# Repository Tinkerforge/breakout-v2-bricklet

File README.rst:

Breakout Bricklet 2.0
=====================

**This Bricklet is currently in development.**

This repository contains the hardware design files.

Repository Content
------------------

hardware/:
 * Contains KiCad project files and additionally schematics as PDF

Hardware
--------

The hardware is designed with the open source EDA Suite KiCad
(http://www.kicad.org). Before you are able to open the files,
you have to install the Tinkerforge kicad-libraries
(https://github.com/Tinkerforge/kicad-libraries). You can either clone
them directly in hardware/ or clone them in a separate folder and
symlink them into hardware/
(ln -s kicad_path/kicad-libraries project_path/hardware). After that you
can open the .pro file in hardware/ with KiCad and from there view and
modify the schematics and the PCB layout.

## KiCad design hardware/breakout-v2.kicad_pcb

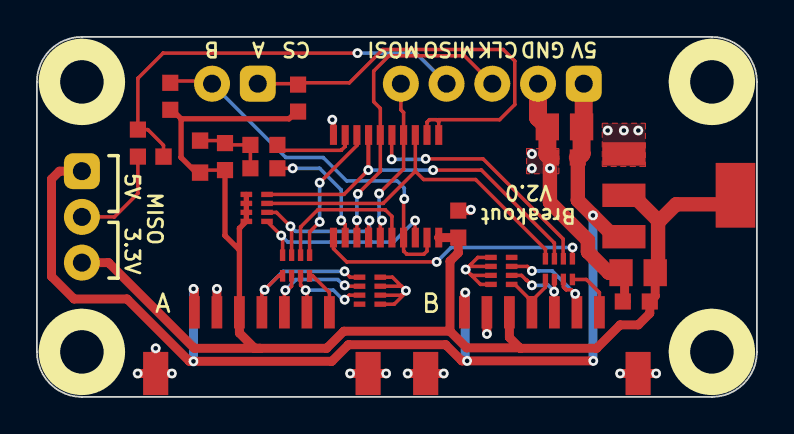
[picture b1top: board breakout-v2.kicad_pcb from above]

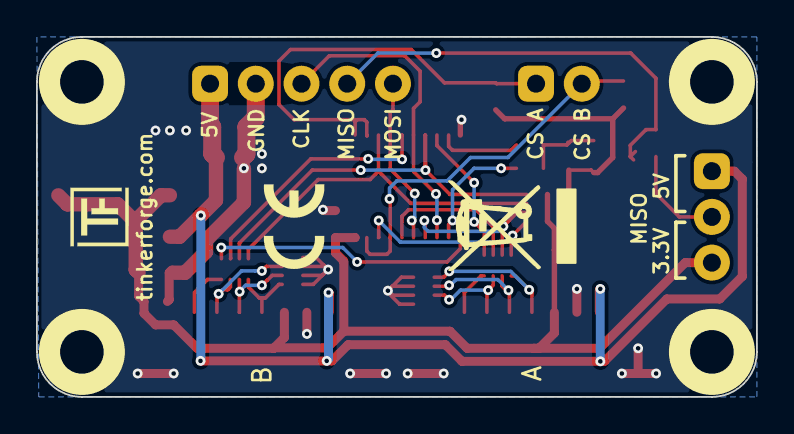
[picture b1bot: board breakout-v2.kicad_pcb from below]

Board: 2 copper layers, 40.0 x 20.0 mm, 30 parts (2 on the bottom side), 28 nets.

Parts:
C1, C3: 10uF; C0805E
C2, C4: 1uF; C0603F
C5: 100nF; C0603F
CP1, CP2: 220pF; 4X0402
P1: Port A; CON-SENSOR2
P2: CONN_01X05; pin_array_1x5-P2mm_D1mm
P3: CONN_01X02; pin_array_1x2-P2mm_D1mm
P4: CONN_01X03; pin_array_1x3-P2mm_D1mm
P5: Port B; CON-SENSOR2
Q1: 2N7002; SOT23GDS
R1, R2, R3, R4: 10k; R0603F
R5, R6: 100; R0603F
RP1, RP2: 82; 4X0402
RP3: 100k; 4X0402
U1: LD1117; SOT-223
U2: 74AHC244; TSSOP20
U3, U4, U5, U6: DRILL; DRILL_NP
VAL: CE_5mm
VAL#2: WEEE_7mm

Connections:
+3.3VP: C3.1, C4.1, C5.1, P1.3, P4.3, P5.3, Q1.G, R2.1, R3.1, R4.1, RP3.1, RP3.2, RP3.3, RP3.4, U1.2, U2.20
+5V: C1.1, C2.1, P1.1, P2.1, P4.1, P5.1, U1.3
CLK: P2.3, U2.6, U2.13
CS_A: P3.1, R4.2, U2.1, U2.2
CS_B: P3.2, R3.2, U2.17, U2.19
GND: C1.2, C2.2, C3.2, C4.2, C5.2, CP1.5, CP1.6, CP1.7, CP1.8, CP2.5, CP2.6, CP2.7, CP2.8, P1.2, P1.EP, P2.2, P5.2, P5.EP, U1.1, U2.10
MISO: P2.4, Q1.D, R1.2
MOSI: P2.5, U2.4, U2.15
unnamed: CP1.1, P1.4, RP1.5
unnamed: CP1.2, P1.5, RP1.6
unnamed: CP1.3, P1.6, RP1.7
unnamed: CP2.1, P5.4, RP2.5
unnamed: CP2.2, P5.5, RP2.6
unnamed: CP2.3, P5.6, RP2.7
unnamed: P1.7, RP1.8
unnamed: P4.2, R1.1
unnamed: P5.7, RP2.8
unnamed: Q1.S, R2.2, R5.2, R6.2
unnamed: R5.1, U2.12
unnamed: R6.1, U2.9
unnamed: RP1.1, U2.8
unnamed: RP1.2, U2.16
unnamed: RP1.3, RP3.6, U2.14
unnamed: RP1.4, RP3.5, U2.18
unnamed: RP2.1, U2.11
unnamed: RP2.2, U2.5
unnamed: RP2.3, RP3.8, U2.7
unnamed: RP2.4, RP3.7, U2.3

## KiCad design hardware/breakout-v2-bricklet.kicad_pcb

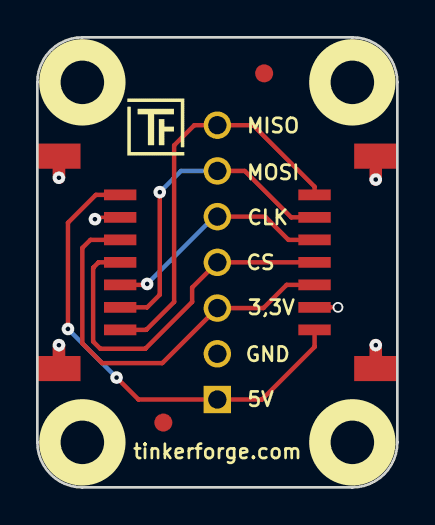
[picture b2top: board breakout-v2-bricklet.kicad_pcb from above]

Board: 2 copper layers, 20.0 x 25.0 mm, 10 parts (1 on the bottom side), 7 nets.

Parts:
Fiducial_Mark: VAL**; Fiducial_Mark
Fiducial_Mark#2: VAL**; Fiducial_Mark
P1, P3: CON-SENSOR2
P2: CONN_01X07; PIN_ARRAY-7X1
U1, U2, U3, U4: DRILL; DRILL_NP
VAL: CE_5mm

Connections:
GND: P1.2, P1.EP, P2.2, P3.2, P3.EP
unnamed: P1.1, P2.1, P3.1
unnamed: P1.3, P2.3, P3.3
unnamed: P1.4, P2.4, P3.4
unnamed: P1.5, P2.5, P3.5
unnamed: P1.6, P2.6, P3.6
unnamed: P1.7, P2.7, P3.7

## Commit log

2017-02-27 Add readme
2017-02-27 Initial check in
2017-02-27 Add schematic
2017-02-27 Add PCB
2017-02-28 Add WEEE, CE and TF logos
2017-02-28 Fix labeling and add fiducial marks
2017-03-01 Fix CE logo
2018-02-20 Add .gitignore
2018-02-20 Cleanup KiCad libraries config
    Ensure LibDir=kicad-libraries and LibName1=tinkerforge.
    Remove special library.
2018-05-14 Add 3d information
2018-05-14 Add 3d model (*.FCStd & *.step)
2019-05-13 fix filenames
2020-06-18 new schematic
2020-06-19 new design
2020-06-22 edited silksreen
2020-07-01 changed design
2020-07-02 switched MISO and MOSI pin
2020-09-09 fix bottom layer
2021-10-25 Update KiCad link
    https://www.kicad.org/blog/2021/10/Avoid-links-to-former-kicad-domain/

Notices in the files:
hardware/breakout-v2-bricklet.kicad_pcb:
Licensed under CERN OHL v.1.1
Copyright (©) 2017, L.Lauer
hardware/breakout-v2.kicad_pcb:
Copyright (©) 2020, T.Schneidermann
Copyright Tinkerforge GmbH 2020.
This documentation describes Open Hardware and is licensed under the
CERN OHL v. 1.1.
